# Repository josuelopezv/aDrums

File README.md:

**A-Drums** is a completly Open Source, Advance Drum MIDI Trigger based on Arduino Leonardo Micro Pro. The idea came after seeing solutions like MegaDRUM but it was closed source. The hardware is open source as well including Eagle Schematics and Eagle Board Layout. It is easy to use and build while being a robust product.

## Features
* 37 Input Triggers with 18 small audio jack connectors
* It's a simple USB Device without need to install any drivers to run it reports as a MIDI Device
* Positional sensing
* Fully Customizable
* Small Form Factor
* Comes with a nice easy to use GUI Manager
* Saves settings to EEPROM
* Compatible with EZ Drummer, Addictive Drums, Fruity Loops, etc.
* Cross Platform (Windows/Linux/Mac)
* Can be configured from Android or iOS

## Price and Bill of Materials
- [Arduino Leonardo Pro Micro](https://www.sparkfun.com/products/12640)		$4.13
- PCB Board		$8.30
- [Audio Jacks](http://www.ebay.com/itm/141778008302?_trksid=p2060353.m2749.l2649&ssPageName=STRK%3AMEBIDX%3AIT)		$6.87
- [Rest of electronics]		$2.5

### Total **$19.24**

I will be adding tutorials on how to build the DIY 3D Printed Drum Set, how to connect with EZ Drummer and Addictive Drums using ASIO4ALL, and aDrums Manager User Manual

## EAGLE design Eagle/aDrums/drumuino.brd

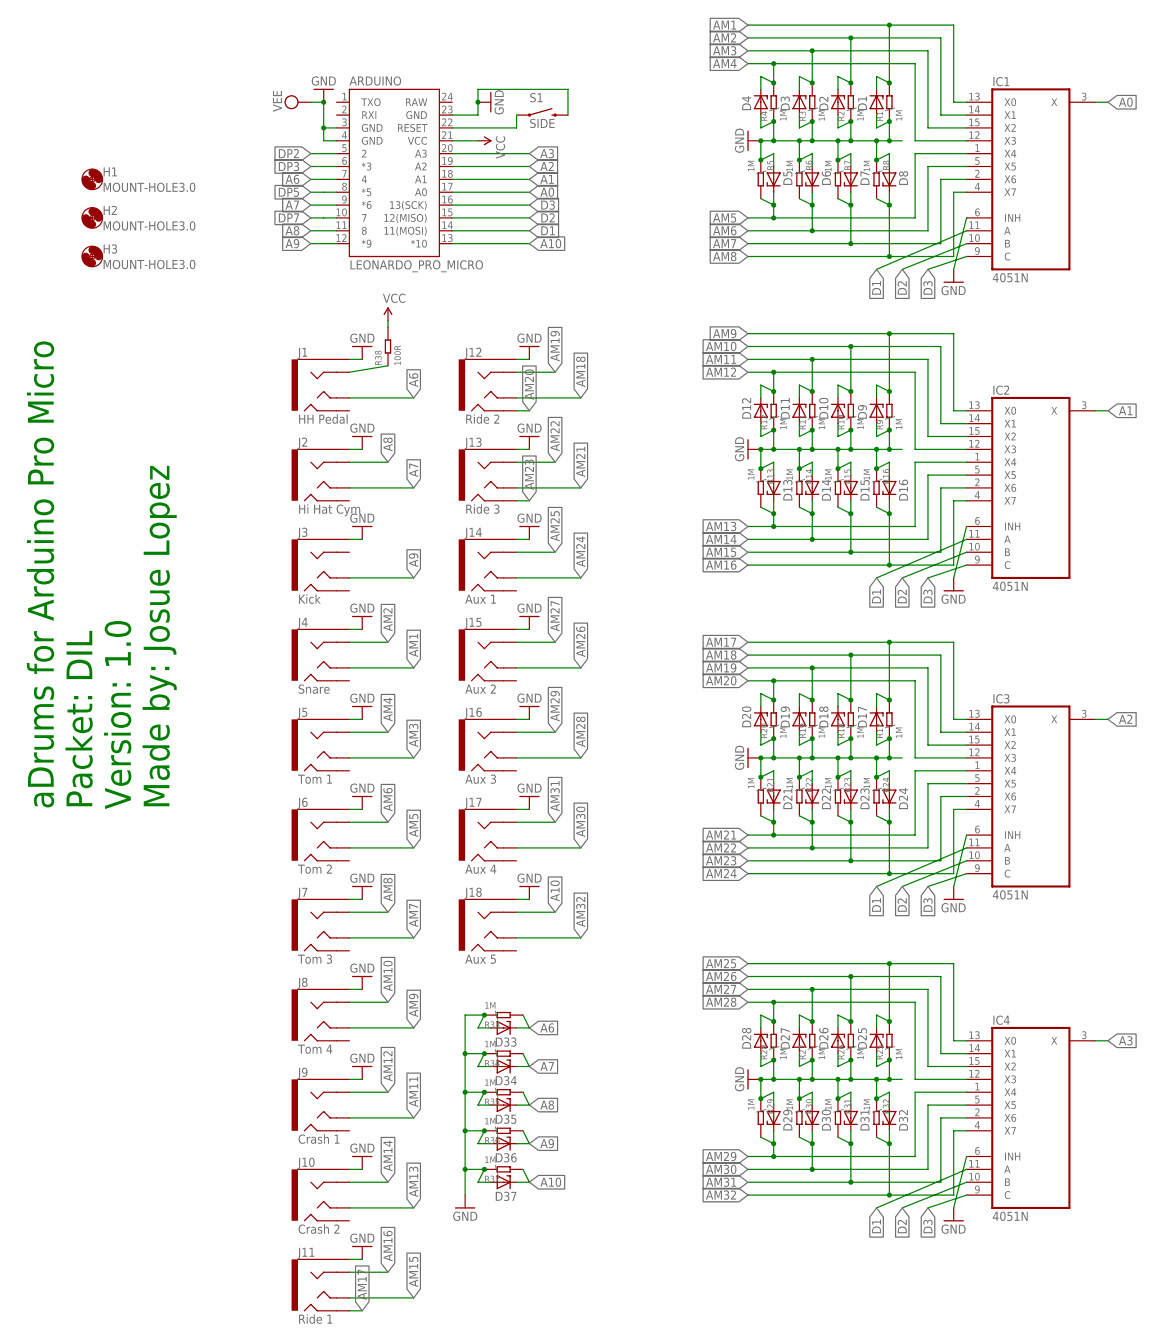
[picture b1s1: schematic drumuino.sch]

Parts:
ARDUINO: LEONARDO_PRO_MICRO; ARDUINO_PRO_MICRO
D1, D2, D3, D4, D5, D6, D7, D8, D9, D10, D11, D12, D13, D14, D15, D16, D17, D18, D19, D20, D21, D22, D23, D24, D25, D26, D27, D28, D29, D30, D31, D32, D33, D34, D35, D36, D37: \; DO41-7.6
H1, H2, H3: MOUNT-HOLE3.0; 3,0
IC1, IC2, IC3, IC4: 4051N; DIL16
J1: HH Pedal; AUDIO-JACK-TRRS-DIL
J2: Hi Hat Cym; AUDIO-JACK-TRRS-DIL
J3: Kick; AUDIO-JACK-TRRS-DIL
J4: Snare; AUDIO-JACK-TRRS-DIL
J5: Tom 1; AUDIO-JACK-TRRS-DIL
J6: Tom 2; AUDIO-JACK-TRRS-DIL
J7: Tom 3; AUDIO-JACK-TRRS-DIL
J8: Tom 4; AUDIO-JACK-TRRS-DIL
J9: Crash 1; AUDIO-JACK-TRRS-DIL
J10: Crash 2; AUDIO-JACK-TRRS-DIL
J11: Ride 1; AUDIO-JACK-TRRS-DIL
J12: Ride 2; AUDIO-JACK-TRRS-DIL
J13: Ride 3; AUDIO-JACK-TRRS-DIL
J14: Aux 1; AUDIO-JACK-TRRS-DIL
J15: Aux 2; AUDIO-JACK-TRRS-DIL
J16: Aux 3; AUDIO-JACK-TRRS-DIL
J17: Aux 4; AUDIO-JACK-TRRS-DIL
J18: Aux 5; AUDIO-JACK-TRRS-DIL
R1, R2, R3, R4, R5, R6, R7, R8, R9, R10, R11, R12, R13, R14, R15, R16, R17, R18, R19, R20, R21, R22, R23, R24, R25, R26, R27, R28, R29, R30, R31, R32, R33, R34, R35, R36, R37: 1M; R0207_7
R38: 100R; R0207_7
S1: SIDE; TACTILE-PTH-SIDEEZ

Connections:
A0: ARDUINO.17 (A0), IC1.3 (X)
A1: ARDUINO.18 (A1), IC2.3 (X)
A2: ARDUINO.19 (A2), IC3.3 (X)
A3: ARDUINO.20 (A3), IC4.3 (X)
A6: ARDUINO.7 (4), D33.C, J1.TIP, R33.2
A7: ARDUINO.9 (*6), D34.C, J2.TIP, R34.2
A8: ARDUINO.11 (8), D35.C, J2.RING1, R35.2
A9: ARDUINO.12 (*9), D36.C, J3.TIP, R36.2
A10: ARDUINO.13 (*10), D37.C, J18.RING1, R37.2
AM1: D1.C, IC1.13 (X0), J4.TIP, R1.2
AM2: D2.C, IC1.14 (X1), J4.RING1, R2.2
AM3: D3.C, IC1.15 (X2), J5.TIP, R3.2
AM4: D4.C, IC1.12 (X3), J5.RING1, R4.2
AM5: D5.C, IC1.1 (X4), J6.TIP, R5.2
AM6: D6.C, IC1.5 (X5), J6.RING1, R6.2
AM7: D7.C, IC1.2 (X6), J7.TIP, R7.2
AM8: D8.C, IC1.4 (X7), J7.RING1, R8.2
AM9: D9.C, IC2.13 (X0), J8.TIP, R9.2
AM10: D10.C, IC2.14 (X1), J8.RING1, R10.2
AM11: D11.C, IC2.15 (X2), J9.TIP, R11.2
AM12: D12.C, IC2.12 (X3), J9.RING1, R12.2
AM13: D13.C, IC2.1 (X4), J10.TIP, R13.2
AM14: D14.C, IC2.5 (X5), J10.RING1, R14.2
AM15: D15.C, IC2.2 (X6), J11.TIP, R15.2
AM16: D16.C, IC2.4 (X7), J11.RING1, R16.2
AM17: D17.C, IC3.13 (X0), J11.RING2, R17.2
AM18: D18.C, IC3.14 (X1), J12.TIP, R18.2
AM19: D19.C, IC3.15 (X2), J12.RING1, R19.2
AM20: D20.C, IC3.12 (X3), J12.RING2, R20.2
AM21: D21.C, IC3.1 (X4), J13.TIP, R21.2
AM22: D22.C, IC3.5 (X5), J13.RING1, R22.2
AM23: D23.C, IC3.2 (X6), J13.RING2, R23.2
AM24: D24.C, IC3.4 (X7), J14.TIP, R24.2
AM25: D25.C, IC4.13 (X0), J14.RING1, R25.2
AM26: D26.C, IC4.14 (X1), J15.TIP, R26.2
AM27: D27.C, IC4.15 (X2), J15.RING1, R27.2
AM28: D28.C, IC4.12 (X3), J16.TIP, R28.2
AM29: D29.C, IC4.1 (X4), J16.RING1, R29.2
AM30: D30.C, IC4.5 (X5), J17.TIP, R30.2
AM31: D31.C, IC4.2 (X6), J17.RING1, R31.2
AM32: D32.C, IC4.4 (X7), J18.TIP, R32.2
D1: ARDUINO.14 (11(MOSI)), IC1.11 (A), IC2.11 (A), IC3.11 (A), IC4.11 (A)
D2: ARDUINO.15 (12(MISO)), IC1.10 (B), IC2.10 (B), IC3.10 (B), IC4.10 (B)
D3: ARDUINO.16 (13(SCK)), IC1.9 (C), IC2.9 (C), IC3.9 (C), IC4.9 (C)
DP2: ARDUINO.5 (2)
DP3: ARDUINO.6 (*3)
DP5: ARDUINO.8 (*5)
DP7: ARDUINO.10 (7)
GND: ARDUINO.3 (GND), ARDUINO.4 (GND), ARDUINO.23 (GND), D1.A, D2.A, D3.A, D4.A, D5.A, D6.A, D7.A, D8.A, D9.A, D10.A, D11.A, D12.A, D13.A, D14.A, D15.A, D16.A, D17.A, D18.A, D19.A, D20.A, D21.A, D22.A, D23.A, D24.A, D25.A, D26.A, D27.A, D28.A, D29.A, D30.A, D31.A, D32.A, D33.A, D34.A, D35.A, D36.A, D37.A, IC1.6 (INH), IC1.7 (VEE), IC1.8 (GND), IC2.6 (INH), IC2.7 (VEE), IC2.8 (GND), IC3.6 (INH), IC3.7 (VEE), IC3.8 (GND), IC4.6 (INH), IC4.7 (VEE), IC4.8 (GND), J1.2EARTH (EARTH), J1.EARTH, J2.2EARTH (EARTH), J2.EARTH, J3.2EARTH (EARTH), J3.EARTH, J4.2EARTH (EARTH), J4.EARTH, J5.2EARTH (EARTH), J5.EARTH, J6.2EARTH (EARTH), J6.EARTH, J7.2EARTH (EARTH), J7.EARTH, J8.2EARTH (EARTH), J8.EARTH, J9.2EARTH (EARTH), J9.EARTH, J10.2EARTH (EARTH), J10.EARTH, J11.2EARTH (EARTH), J11.EARTH, J12.2EARTH (EARTH), J12.EARTH, J13.2EARTH (EARTH), J13.EARTH, J14.2EARTH (EARTH), J14.EARTH, J15.2EARTH (EARTH), J15.EARTH, J16.2EARTH (EARTH), J16.EARTH, J17.2EARTH (EARTH), J17.EARTH, J18.2EARTH (EARTH), J18.EARTH, R1.1, R2.1, R3.1, R4.1, R5.1, R6.1, R7.1, R8.1, R9.1, R10.1, R11.1, R12.1, R13.1, R14.1, R15.1, R16.1, R17.1, R18.1, R19.1, R20.1, R21.1, R22.1, R23.1, R24.1, R25.1, R26.1, R27.1, R28.1, R29.1, R30.1, R31.1, R32.1, R33.1, R34.1, R35.1, R36.1, R37.1, S1.2
HHC_TIP: J1.RING1, R38.1
unnamed: ARDUINO.22 (RESET), S1.1
VCC: ARDUINO.21 (VCC), IC1.16 (VCC), IC2.16 (VCC), IC3.16 (VCC), IC4.16 (VCC), R38.2

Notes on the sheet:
aDrums for Arduino Pro Micro Packet: DIL Version: 1.0 Made by: Josue Lopez

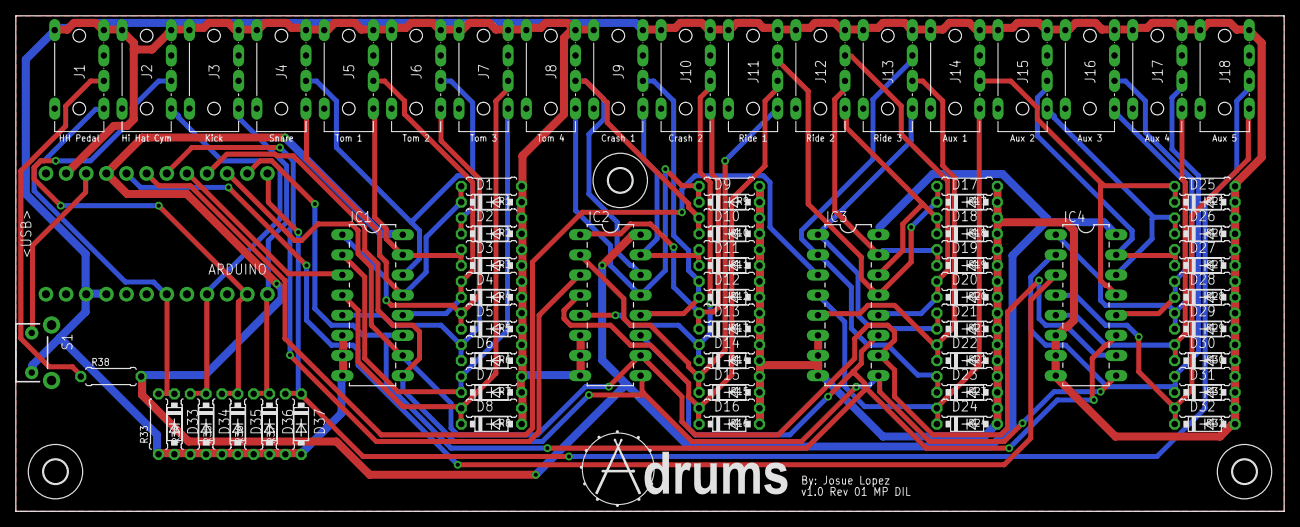
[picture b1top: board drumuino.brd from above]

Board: 2 copper layers, 160.0 x 62.5 mm, 102 parts (0 on the bottom side), 48 nets.

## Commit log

2016-10-19 Add .gitignore and .gitattributes.
2016-10-19 Add project files.
2016-10-19 init
2016-10-19 working after tests
2016-10-19 adding eagle files
2016-10-19 Create gh-pages branch via GitHub
2016-10-19 ver 0.9.1
2016-10-20 add web manager
2021-04-21 Create LICENSE

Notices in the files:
parts and their libraries:
SparkFun-Boards: Licensing: Creative Commons ShareAlike 4.0 International - https://creativecommons.org/licenses/by-sa/4.0
